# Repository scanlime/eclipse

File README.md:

# Eclipse

An interactive sculptural work.

2015, Micah Elizabeth Scott

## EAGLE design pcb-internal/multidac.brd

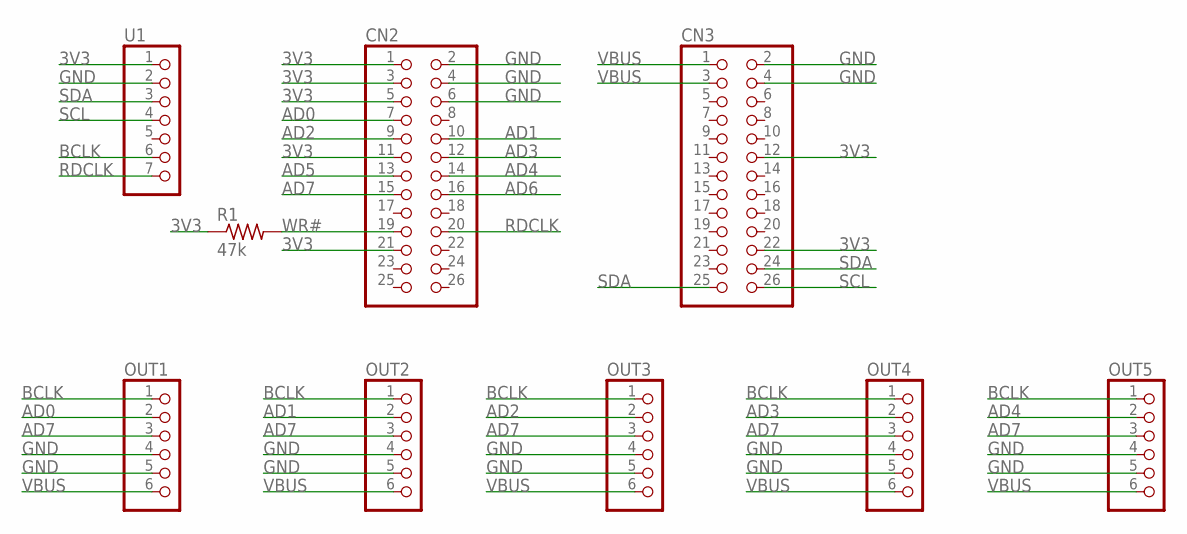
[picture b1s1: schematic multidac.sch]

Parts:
CN2, CN3: PINHD-2X13; 2X13
OUT1, OUT2, OUT3, OUT4, OUT5: PINHD-1X6; 1X06
R1: 47k; R1206
U1: PINHD-1X7; 1X07

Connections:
3V3: CN2.1, CN2.3, CN2.5, CN2.11, CN2.21, CN3.12, CN3.22, R1.1, U1.1
AD0: CN2.7, OUT1.2
AD1: CN2.10, OUT2.2
AD2: CN2.9, OUT3.2
AD3: CN2.12, OUT4.2
AD4: CN2.14, OUT5.2
AD5: CN2.13
AD6: CN2.16
AD7: CN2.15, OUT1.3, OUT2.3, OUT3.3, OUT4.3, OUT5.3
BCLK: OUT1.1, OUT2.1, OUT3.1, OUT4.1, OUT5.1, U1.6
GND: CN2.2, CN3.2, CN3.4, OUT1.4, OUT1.5, OUT2.4, OUT2.5, OUT3.4, OUT3.5, OUT4.4, OUT4.5, OUT5.4, OUT5.5, U1.2
RDCLK: CN2.20, U1.7
SCL: CN3.26, U1.4
SDA: CN3.24, CN3.25, U1.3
VBUS: CN3.1, CN3.3, OUT1.6, OUT2.6, OUT3.6, OUT4.6, OUT5.6
WR#: CN2.19, R1.2

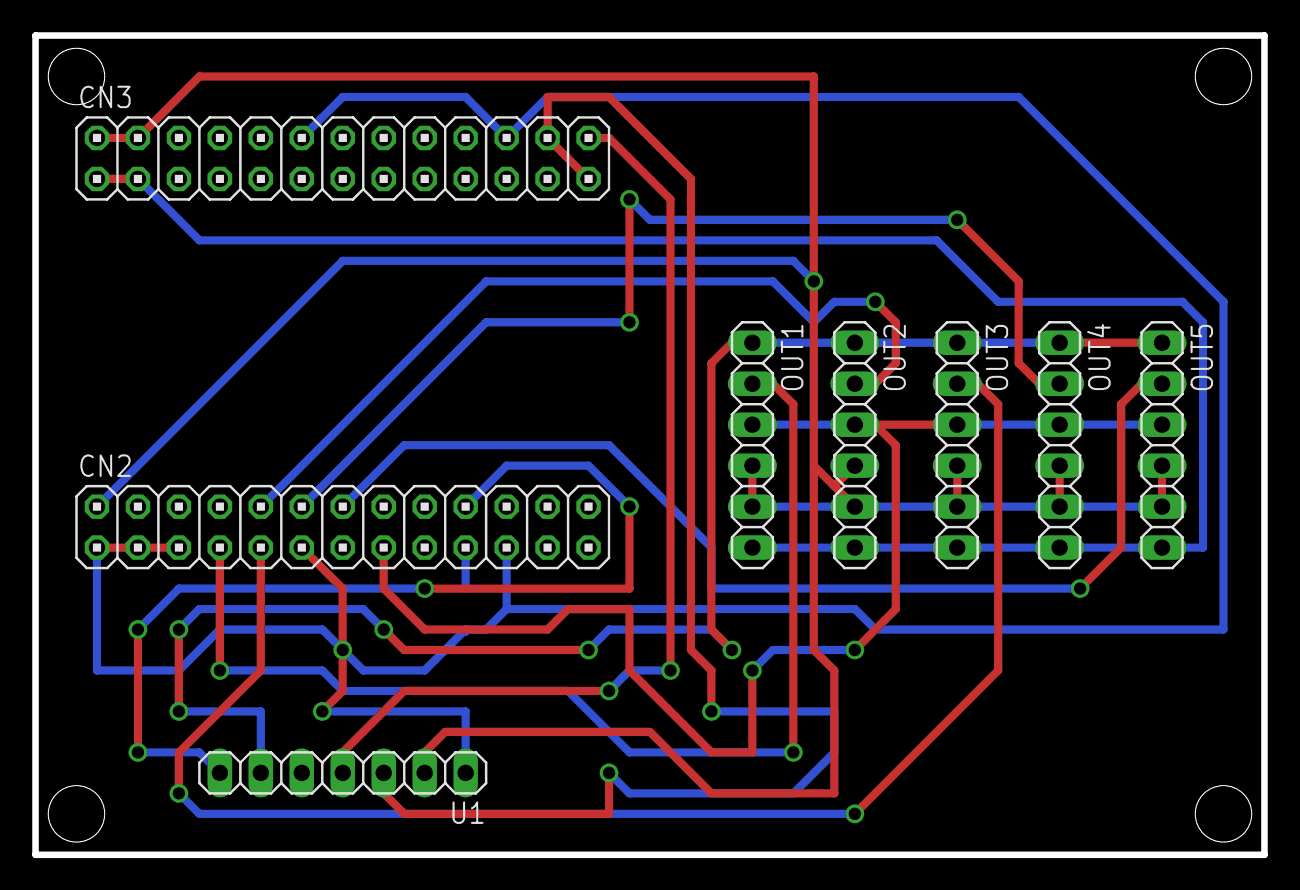
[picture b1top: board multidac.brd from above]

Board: 2 copper layers, 76.2 x 50.8 mm, 9 parts (1 on the bottom side), 14 nets.

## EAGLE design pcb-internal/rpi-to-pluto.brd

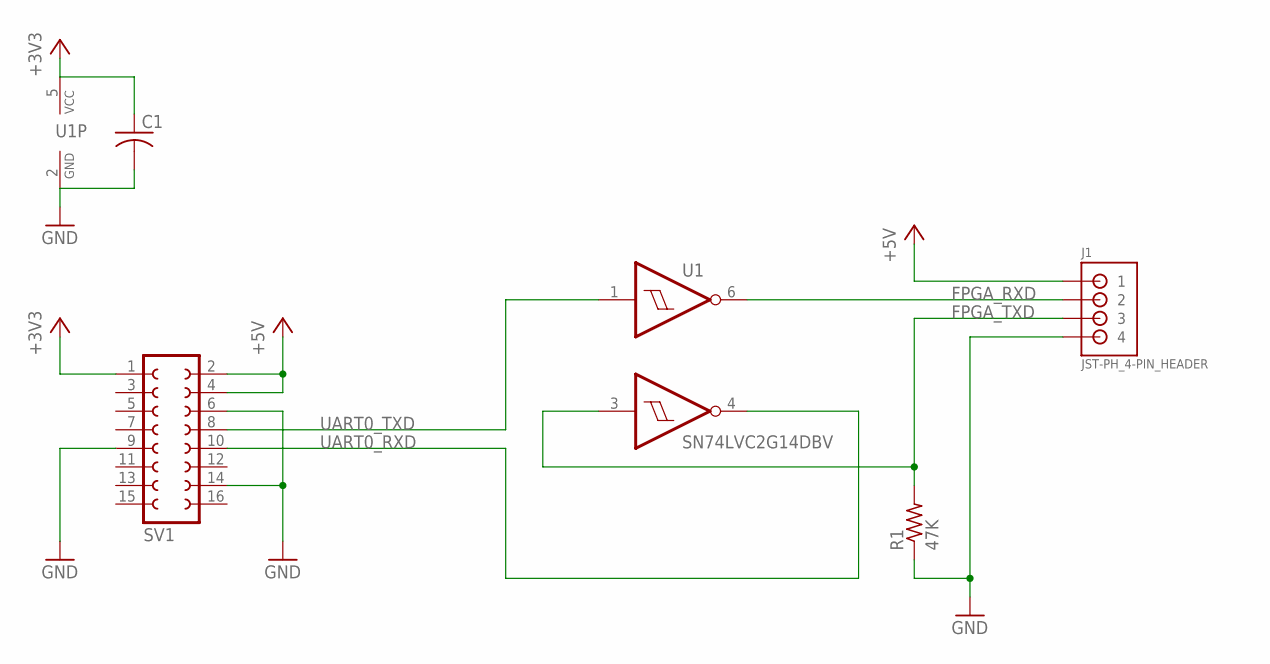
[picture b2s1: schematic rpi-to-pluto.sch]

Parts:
C1: C-USC0805; C0805
J1: JST-PH_4-PIN_HEADER; JST_B4B-PH_HEADER
R1: 47K; R0805
SV1: FE08-2
U1: SN74LVC2G14DBV; SOT23-6

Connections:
+3V3: C1.1, SV1.1, U1.5 (VCC)
+5V: J1.P1 (1), SV1.2, SV1.4
FPGA_RXD: J1.P2 (2), U1.6 (1Y)
FPGA_TXD: J1.P3 (3), R1.2, U1.3 (2A)
GND: C1.2, J1.P4 (4), R1.1, SV1.6, SV1.9, SV1.14, U1.2 (GND)
UART0_RXD: SV1.10, U1.4 (2Y)
UART0_TXD: SV1.8, U1.1 (1A)

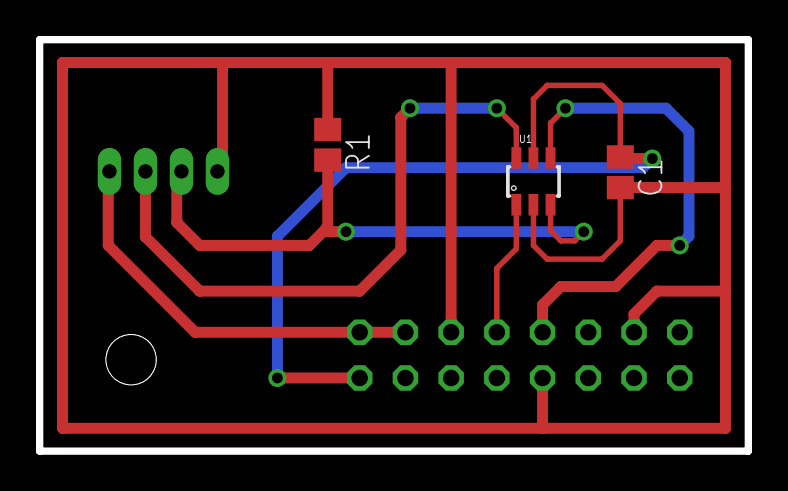
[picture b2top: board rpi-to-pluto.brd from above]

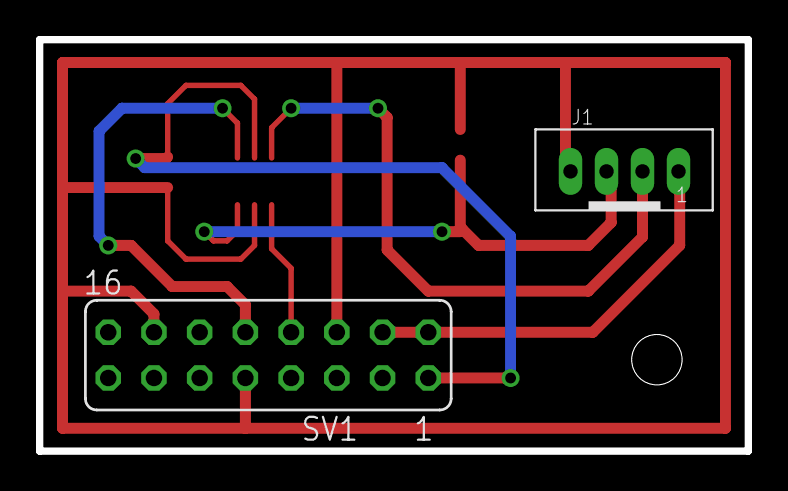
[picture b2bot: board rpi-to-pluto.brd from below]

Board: 2 copper layers, 39.4 x 22.9 mm, 5 parts (2 on the bottom side), 7 nets.

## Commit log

2015-09-22 Initial import into version control
2015-09-22 Clean up README
2015-09-22 Preserve old revisions of the CAD models in git history only
2015-09-22 Remove spurious grasshopper file
2015-09-22 Remove bogus DS_Store
2015-09-22 Rename PCB directories
2015-09-23 Ignore EAGLE temp files
2015-09-23 Interface board, Raspberry Pi to KNJN Pluto FPGA
2015-09-23 Debugging rPI/FPGA connection
2015-09-23 New rpi-to-pluto board using the 74LVC2G14
2015-09-23 Notes on speaker design
2015-09-23 More ignorables
2015-09-23 New 3-part centering jig for locating the pillarjig
    So many jigs
2015-09-24 Ignore more FPGA junk files
2015-09-24 Switch to white PLA for the centering jig
    This is cheaper and prints easier/faster.
2015-09-24 First pass at a working FPGA design
    It barely fits!
2015-10-02 Final standoff design
2015-10-02 Single-strut gcode
2015-10-02 Final cut files for rpi-to-pluto
2015-10-02 Woodworking layout
2015-10-02 PCB mill files for the speakers so far
2015-10-02 Bookmark
2015-10-02 Terrible first draft at a whisker design
2015-10-02 Triangle PCB outlines
2015-10-03 Finished milling necessary for speaker glueup
2015-10-03 New whisker design, hopefully final
    Gcode for a 10up print. Need 60 of these total, one per power wire. This acts as a form for securing the knot that holds each wire securely around its post, and the long whisker portion acts as a lea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
2015-10-04 Triangle tip PCBs milled
2015-10-04 Power distribution PCB design
2015-10-04 Pulled a Syz, flip all the power PCB files
2015-10-04 Milling files for power PCBs
2015-10-05 Mount for 4x Fadecandy boards in the center
2015-10-05 Update power PCB milling files
2015-10-06 Reprint fcsquare, slow down a bit
    Trying to reduce stringing, but it didn't really do much.
    Anyway, this is the final version of the model I used.
2015-10-06 New untested PCB design for a 10-channel USB DAC
    Uses a FT2232H module and 5 stereo I2S DAC boards, with a Si5351 clock
    generator.
2015-10-06 Center and corner brackets for the aluminum
2015-10-06 Config for the Si5351a clock generator
2015-10-06 Shamelessly copy from Ecstatic Epiphany
2015-10-06 Remove optical flow input, remove unused modules
2015-10-06 Data file rearranging
2015-10-06 I think these are sshfs temp files?
2015-10-06 New C++ module to drive the FPGA sensor
    Includes a faster config scheme that seems to match what the KNJN tools use.
2015-10-06 Usable eclsensor readout, config retry
2015-10-07 EEPROM configuration for the FT2232H module
2015-10-07 Removing old spare files from Ecstatic
2015-10-07 Fix output enables in si5351a register map
2015-10-07 Work-in-progress driver for the multidac
    Clock generator is working, and I have some bits coming out
    on the I2S lines. Almost there...
2015-10-07 zomg the dac works
2015-10-07 Probably nothing?
2015-10-07 Move Ableton set into the repo
2015-10-07 Export the okay tracks
2015-10-07 Loop mixer!
2015-10-07 so quiet
2015-10-07 Startup scripts based on Ecstatic Epiphany's repo
2015-10-07 Startup files and fcserver config stub
2015-10-08 Fine, just use a dumb plastic ring to hold in the power supplies.
2015-10-08 Aluminum mounting plate for the power electronics
2015-10-08 Placeholder software with no interaction
2015-10-08 Quiet the FC LEDs
2015-10-09 Start integration with sensor, enough to display output on stdout
2015-10-09 oops, can't consolidate packets like this for debug
2015-10-10 Longer audio buffers
    Not sure if it's my imagination, but I think i hear it popping every so often.
2015-10-10 Mixer config from the json, finally
2015-10-12 Frontal mapping
2015-10-12 Toss more things that don't work
2015-10-12 Some easy randomization in the mixer for now
2015-10-12 Last of the changes from Dropbox
2019-03-19 Remove mac droppings
